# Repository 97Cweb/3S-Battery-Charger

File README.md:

# 3S-Battery-Charger
An arduino powered 3S battery charger controlling the input current to a CC/CV regulator preventing overcharge and allowing battery topup every five minutes

# CPS-V2 Folder
Contains PCB files to be printed. Made in KiCad so edit using KiCAD

# Sox CPS.ino
Arduino code to run the project

# Components
1 Arduino Nano

1 LM7805 voltage regulator

1 IRLZ44N Mosfet

2 1uF capacitors

1 0.1uF ceramic capacitor

1 100uF capacitor

2 5mm pitch screw terminals capable of holding 12AWG wire

1 JST SH 1x4 connector

1 Adafruit INA260 High or Low Side Voltage, Current, Power Sensor

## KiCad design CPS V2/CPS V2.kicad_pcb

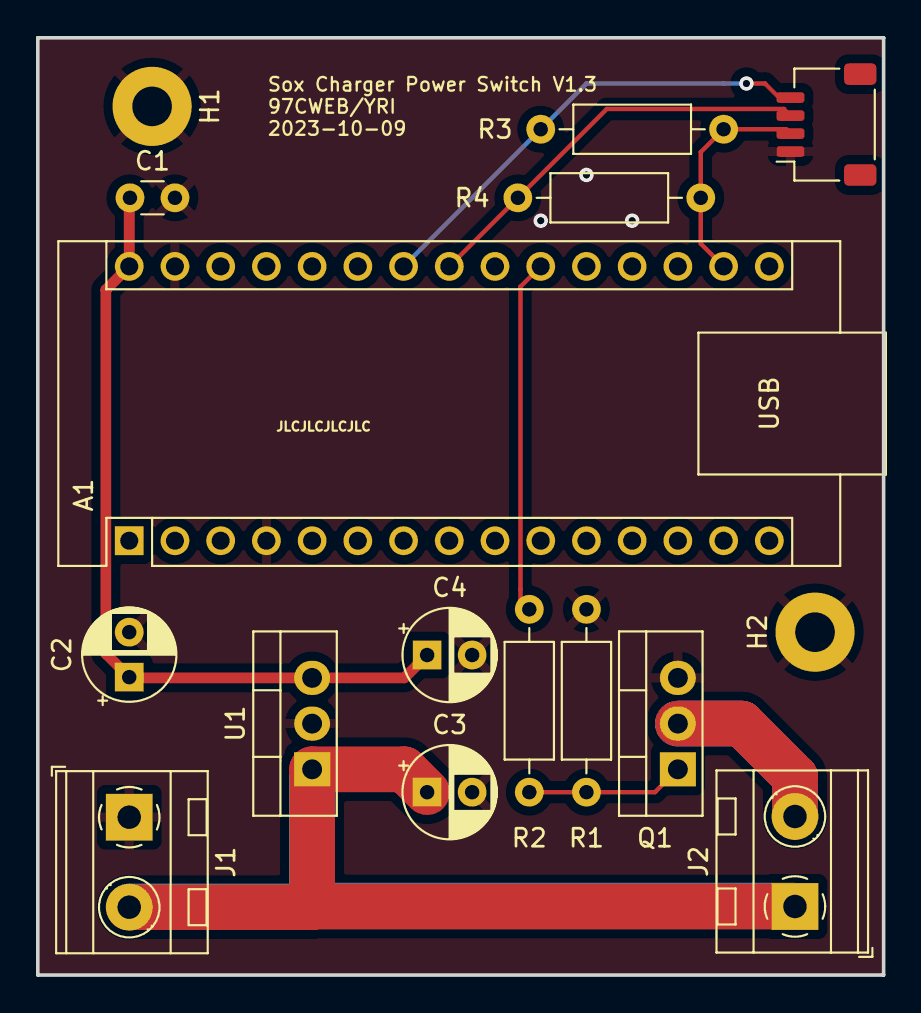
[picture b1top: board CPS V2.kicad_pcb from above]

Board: 2 copper layers, 47.0 x 52.1 mm, 16 parts (0 on the bottom side), 9 nets.

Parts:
A1: Arduino_Nano_v3.x; Arduino_Nano
C1: 0.1uF; C_Disc_D3.0mm_W1.6mm_P2.50mm
C2: 100uF; CP_Radial_D5.0mm_P2.50mm
C3, C4: 1uF; CP_Radial_D5.0mm_P2.50mm
H1, H2: MountingHole_Pad; MountingHole_2.2mm_M2_Pad
J1, J2: Conn_01x02_Socket; TerminalBlock_MetzConnect_Type094_RT03502HBLU_1x02_P5.00mm_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
J3: Conn_01x04_Female; JST_SH_SM04B-SRSS-TB_1x04-1MP_P1.00mm_Horizontal
Q1: IRLZ44N; TO-220-3_Vertical
R1: 100k; R_Axial_DIN0207_L6.3mm_D2.5mm_P10.16mm_Horizontal
R2: 1k; R_Axial_DIN0207_L6.3mm_D2.5mm_P10.16mm_Horizontal
R3, R4: 10k; R_Axial_DIN0207_L6.3mm_D2.5mm_P10.16mm_Horizontal
U1: LM7805_TO220; TO-220-3_Vertical

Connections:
+3.3V: A1.17 (3V3), J3.2, R3.2, R4.2
+5V: A1.30 (VIN), C1.1, C2.1, C4.1, U1.3 (VO)
+20V: C3.1, J1.2, J2.1, U1.1 (VI)
From Batt: J2.2, Q1.2 (D)
GND: A1.4 (GND), A1.29 (GND), C1.2, C2.2, C3.2, C4.2, H1.1, H2.1, J1.1, J3.1, Q1.3 (S), R1.1, U1.2 (GND)
unnamed: A1.21 (A2), R2.2
unnamed: Q1.1 (G), R1.2, R2.1
To SCL: A1.24 (A5), J3.4, R3.1
To SDA: A1.23 (A4), J3.3, R4.1

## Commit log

2023-11-11 Add files via upload
    Initial commit of source code and PCB files
